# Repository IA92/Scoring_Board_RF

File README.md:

# Scoring_Board_RF
An archive of old scoring board project for badminton games.
Note: Code are not well written and managed. Instructions are not fully accurate.

Link to project video: https://youtu.be/4vFphWg7GTI

## Version of arduino files
- scoringBoard.ino: Testing LED panel
- scoringIR.ino, scoringIR_1 and scoringIR_2: 1 LED panel with IR instructions
- HunterBadminton_ProjectRF: 1 LED panel with RF instructions
- HunterBadminton_ProjectRF_Larger: 2 LED panel with RF instructions

## Getting Started with the Project RF Version
### Keyfob
- Get 433MHz key fobs from ebay.
- Use a 433MHz transmitter to transmit the desired code to be cloned by the key fob
- Set the key fob to be in programming mode and clone the transmitted code for each button. 
  - Reference video: https://www.youtube.com/watch?v=l-k_XvkZ0jE
### Code
- Ensure that `buttonCodes` array corresponds to the programmed instructions of the 4 buttons in the key fob

## References for the code in the libraries
- Freetronics lib https://github.com/freetronics/DMD/blob/master/DMD.cpp
- TimerOne lib http://code.google.com/p/arduino-timerone/downloads/list
- RF lib https://github.com/sui77/rc-switch/blob/master/RCSwitch.h

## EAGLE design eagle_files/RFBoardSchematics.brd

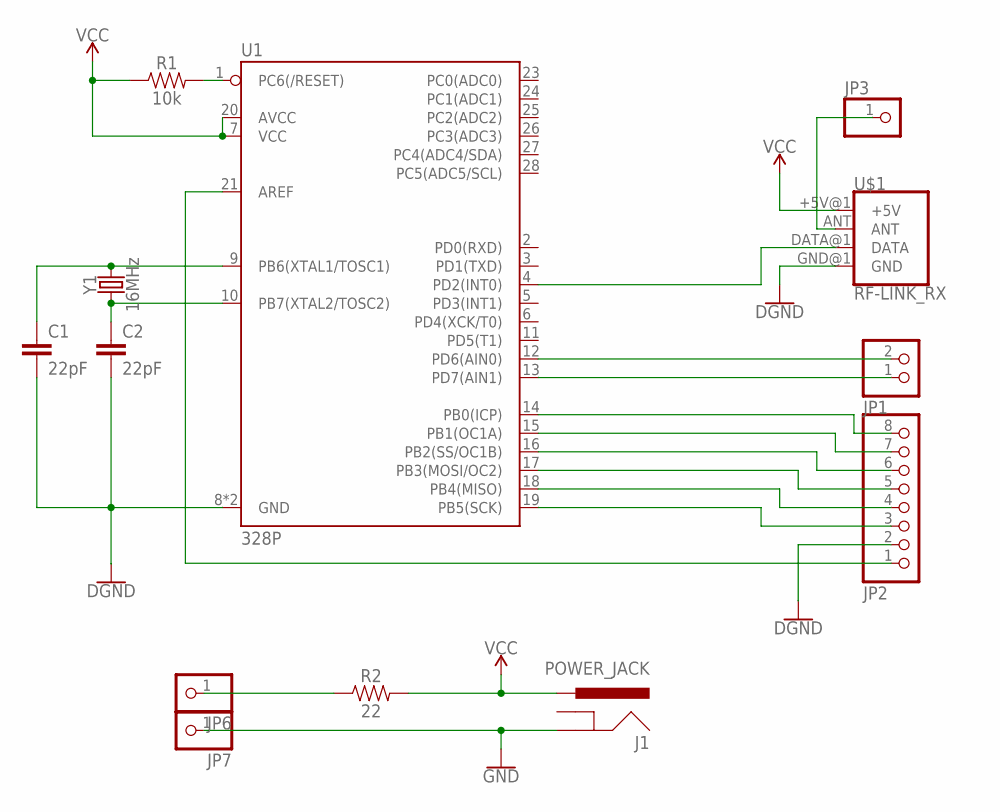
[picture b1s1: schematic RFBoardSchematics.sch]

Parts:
C1, C2: 22pF; CAP-PTH-2.54
J1: POWER_JACK; POWER_JACK_PTH
JP1: PINHD-1X2; 1X02
JP2: PINHD-1X8; 1X08
JP3, JP6, JP7: PINHD-1X1; 1X01
R1: 10k; AXIAL-0.3
R2: 22; AXIAL-0.3
U1: 328P; DIP28
U$1: RF-LINK_RX
Y1: 16MHz; HC49US

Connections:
GND: C1.2, C2.2, J1.GND, JP2.2, JP7.1, U1.8 (GND), U1.22 (GND), U$1.GND@1 (GND)
unnamed: R1.P$2 (2), U1.1 (PC6(/RESET))
unnamed: C1.1, U1.9 (PB6(XTAL1/TOSC1)), Y1.2
unnamed: C2.1, U1.10 (PB7(XTAL2/TOSC2)), Y1.1
unnamed: JP6.1, R2.P$1 (1)
unnamed: JP3.1, U$1.ANT
unnamed: U1.4 (PD2(INT0)), U$1.DATA@1 (DATA)
unnamed: JP1.2, U1.12 (PD6(AIN0))
unnamed: JP1.1, U1.13 (PD7(AIN1))
unnamed: JP2.8, U1.14 (PB0(ICP))
unnamed: JP2.7, U1.15 (PB1(OC1A))
unnamed: JP2.6, U1.16 (PB2(SS/OC1B))
unnamed: JP2.5, U1.17 (PB3(MOSI/OC2))
unnamed: JP2.4, U1.18 (PB4(MISO))
unnamed: JP2.3, U1.19 (PB5(SCK))
unnamed: JP2.1, U1.21 (AREF)
VCC: J1.PWR, R1.P$1 (1), R2.P$2 (2), U1.7 (VCC), U1.20 (AVCC), U$1.+5V@1 (+5V)

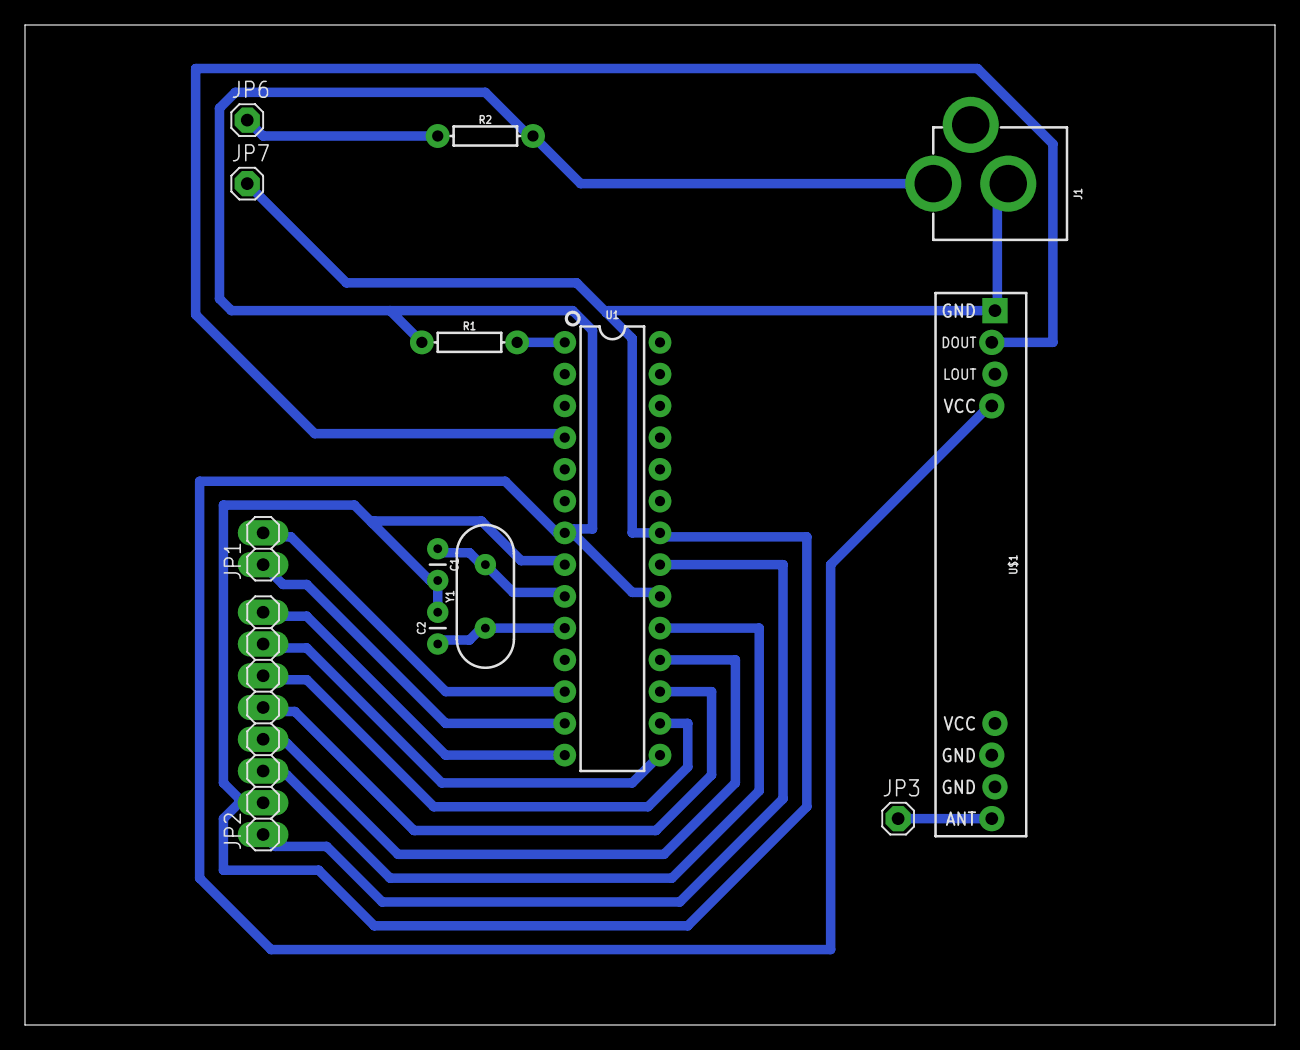
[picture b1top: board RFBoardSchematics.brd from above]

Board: 2 copper layers, 100.0 x 80.0 mm, 13 parts (0 on the bottom side), 17 nets.

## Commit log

2023-06-10 Add all arduino files
2023-06-10 Add photos of the project
2023-06-10 Add eagle schematic and board files.
2023-06-10 Add a document for components
2023-06-10 Add dmd libraries.
    Ref Link: https://github.com/freetronics/DMD
2023-06-10 Upload the rest of the libraries
2023-06-10 Update syntax to import library
2023-06-10 Remove arial_black_16.h include
2023-06-10 Add IRLibAll.h
    It is used in scoringIR arduino files where IR transmitter is used to send the instructions.
2023-06-10 Rename scoringBoardFinal_Larger.ino to HunterBadminton_ProjectRF_Larger.ino
2023-06-13 Add Arial_black_16 to library.
2023-06-13 Add vertical display.
    Without set.
2023-06-13 Update vertical display with set.
    Only display set when it is non-zero.
2023-06-13 Fix bug with unclearing the set when it is 0.
2023-06-13 Fix serve bug. Adjust display.
2023-06-13 Shorten the hold time.

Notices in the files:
parts and their libraries:
SparkFun-Capacitors: Licensing: Creative Commons ShareAlike 4.0 International - https://creativecommons.org/licenses/by-sa/4.0
